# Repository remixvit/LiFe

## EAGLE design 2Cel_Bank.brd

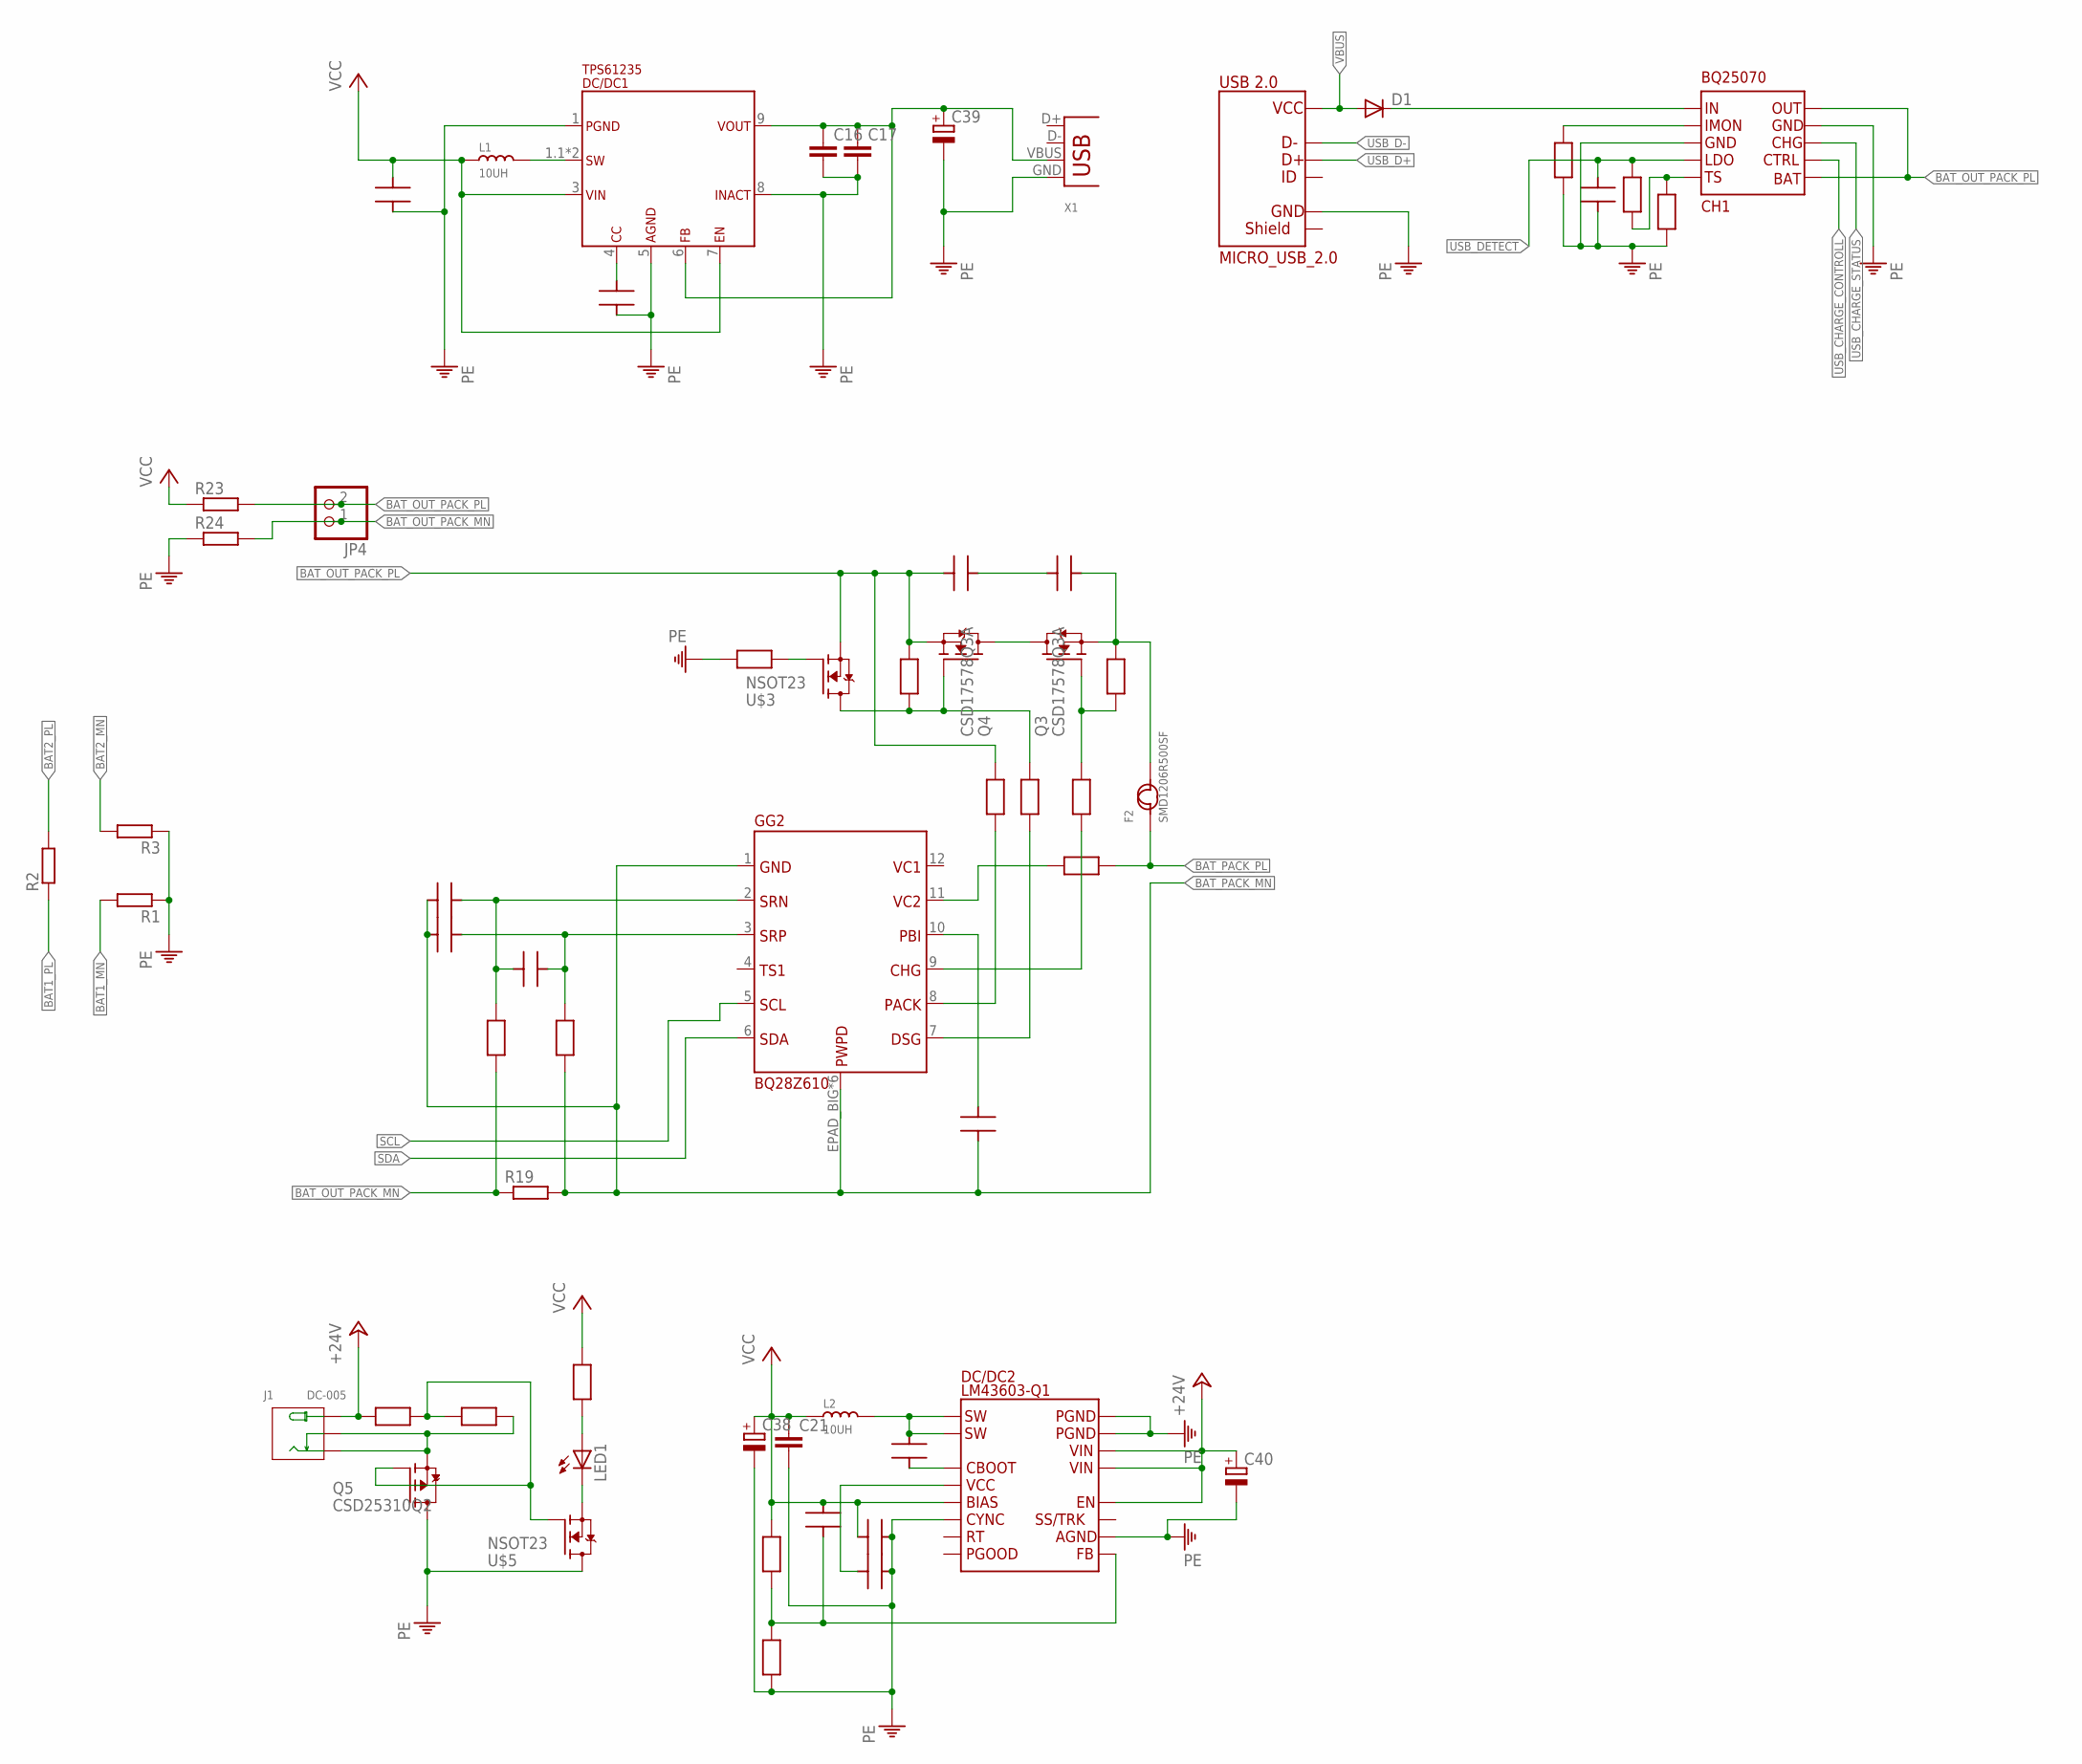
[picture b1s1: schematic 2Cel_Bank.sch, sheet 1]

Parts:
C7, C8, C9, C10, C11, C12, C13, C14, C18, C19, C20, C22, C33: CAP0603; C0603
C16, C17, C21: C-EUC0805; C0805
C38, C39: CPOL-EUSMCA; SMC_A
C40: CPOL-EUSMCD; SMC_D
CH1: BQ25070; DFN10_2X3
D1: DIODE-DO-214AC; DO-214AC
DC/DC1: TPS61235; VQFN9
DC/DC2: LM43603-Q1; HTSSOP16PWP
F2: SMD1206R500SF; F1812
GG2: BQ28Z610; VSON12
J1: DC-005; DCJ3P-14.2X11.0X9.0MM
JP4: PINHD-1X2; 1X02
L1, L2: 10UH; SMD-2P-L6.0XW6.0XH3.0MM
LED1: LEDCHIP-LED0603; CHIP-LED0603
Q3, Q4: CSD17578Q3A; VSONP8
Q5: CSD25310Q2; SON_Q2
R1, R2, R3, R19, R23, R24: R-EU_R1206; R1206
R11, R12, R13, R14, R15, R16, R17, R18, R20, R22, R25, R26, R27, R28, R29, R30, R31: RES0603; R0603
U$3, U$5: NSOT23; SOT23W
USB_CON1: MICRO_USB_2.0; MICRO-USB5+4P-SMD-0.65
X1: USB-A-S

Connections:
+24V: C40.+, DC/DC2.12, DC/DC2.13, DC/DC2.14, J1.+, R25.2
BAT1_MN: R1.2
BAT1_PL: R2.1; also elsewhere on the board
BAT2_MN: R3.2
BAT2_PL: R2.2
BAT_OUT_PACK_MN: JP4.1, R17.1, R19.1, R24.2
BAT_OUT_PACK_PL: C7.1, CH1.P$6, CH1.P$10, JP4.2, Q4.S1 (S), Q4.S2 (S), Q4.S3 (S), R12.2, R15.2, R23.2, U$3.S; also elsewhere on the board
BAT_PACK_MN: C9.1, C10.2, C11.2, GG2.1, GG2.EPAD_BIG, GG2.EPAD_M1, GG2.EPAD_M2, GG2.EPAD_M3, GG2.EPAD_M4, GG2.EPAD_VIA, R18.1, R19.2
BAT_PACK_PL: F2.1, R20.1
unnamed: C8.2, F2.2, Q3.S1 (S), Q3.S2 (S), Q3.S3 (S), R11.2
unnamed: Q3.D1 (D), Q3.D2 (D), Q3.D3 (D), Q3.D4 (D), Q3.D5 (D), Q4.D1 (D), Q4.D2 (D), Q4.D3 (D), Q4.D4 (D), Q4.D5 (D)
unnamed: Q4.G, R12.1, R13.2, U$3.D
unnamed: Q3.G, R11.1, R14.2
unnamed: C7.2, C8.1
unnamed: GG2.9, R14.1
unnamed: GG2.7, R13.1
unnamed: GG2.8, R15.1
unnamed: R16.1, U$3.G
unnamed: C9.2, GG2.10
unnamed: C10.1, C12.2, GG2.2, R17.2
unnamed: C11.1, C12.1, GG2.3, R18.2
unnamed: GG2.11, R20.2
unnamed: J1.-1 (-), J1.-2 (CDN), Q5.4 (D), Q5.D, R26.1
unnamed: DC/DC1.1.1, DC/DC1.1.2, L1.2
unnamed: Q5.3 (G), R25.1, R26.2, U$5.G
unnamed: C13.2, DC/DC1.4
unnamed: C18.2, DC/DC2.1, DC/DC2.2, L2.2
unnamed: C16.1, C17.1, C39.+, DC/DC1.6, DC/DC1.9, X1.VBUS
unnamed: C18.1, DC/DC2.3
unnamed: C19.2, DC/DC2.4
unnamed: C22.2, DC/DC2.9, R27.2, R28.2
unnamed: CH1.P$1, D1.C
unnamed: CH1.P$2, R22.2
unnamed: LED1.C, U$5.S
unnamed: CH1.P$5, R29.2, R30.1
unnamed: LED1.A, R31.2
PE: C13.1, C14.1, C16.2, C17.2, C19.1, C20.1, C21.2, C33.1, C38.-, C39.-, C40.-, CH1.EPAD, CH1.P$3, CH1.P$9, DC/DC1.1, DC/DC1.5, DC/DC1.8, DC/DC2.6, DC/DC2.10, DC/DC2.15, DC/DC2.16, DC/DC2.EXP, Q5.1 (S), Q5.2 (S), Q5.5 (S), Q5.6 (S), Q5.S, R1.1, R3.1, R16.2, R22.1, R24.1, R28.1, R29.1, U$5.D, USB_CON1.5, X1.GND; also elsewhere on the board
SCL: GG2.5; also elsewhere on the board
SDA: GG2.6; also elsewhere on the board
USB_CHARGE_CONTROLL: CH1.P$7; also elsewhere on the board
USB_CHARGE_STATUS: CH1.P$8; also elsewhere on the board
USB_D+: USB_CON1.3; also elsewhere on the board
USB_D-: USB_CON1.2; also elsewhere on the board
USB_DETECT: C33.2, CH1.P$4, R30.2
VBUS: D1.A, USB_CON1.1; also elsewhere on the board
VCC: C14.2, C20.2, C21.1, C22.1, C38.+, DC/DC1.3, DC/DC1.7, DC/DC2.5, L1.1, L2.1, R23.1, R27.1, R31.1

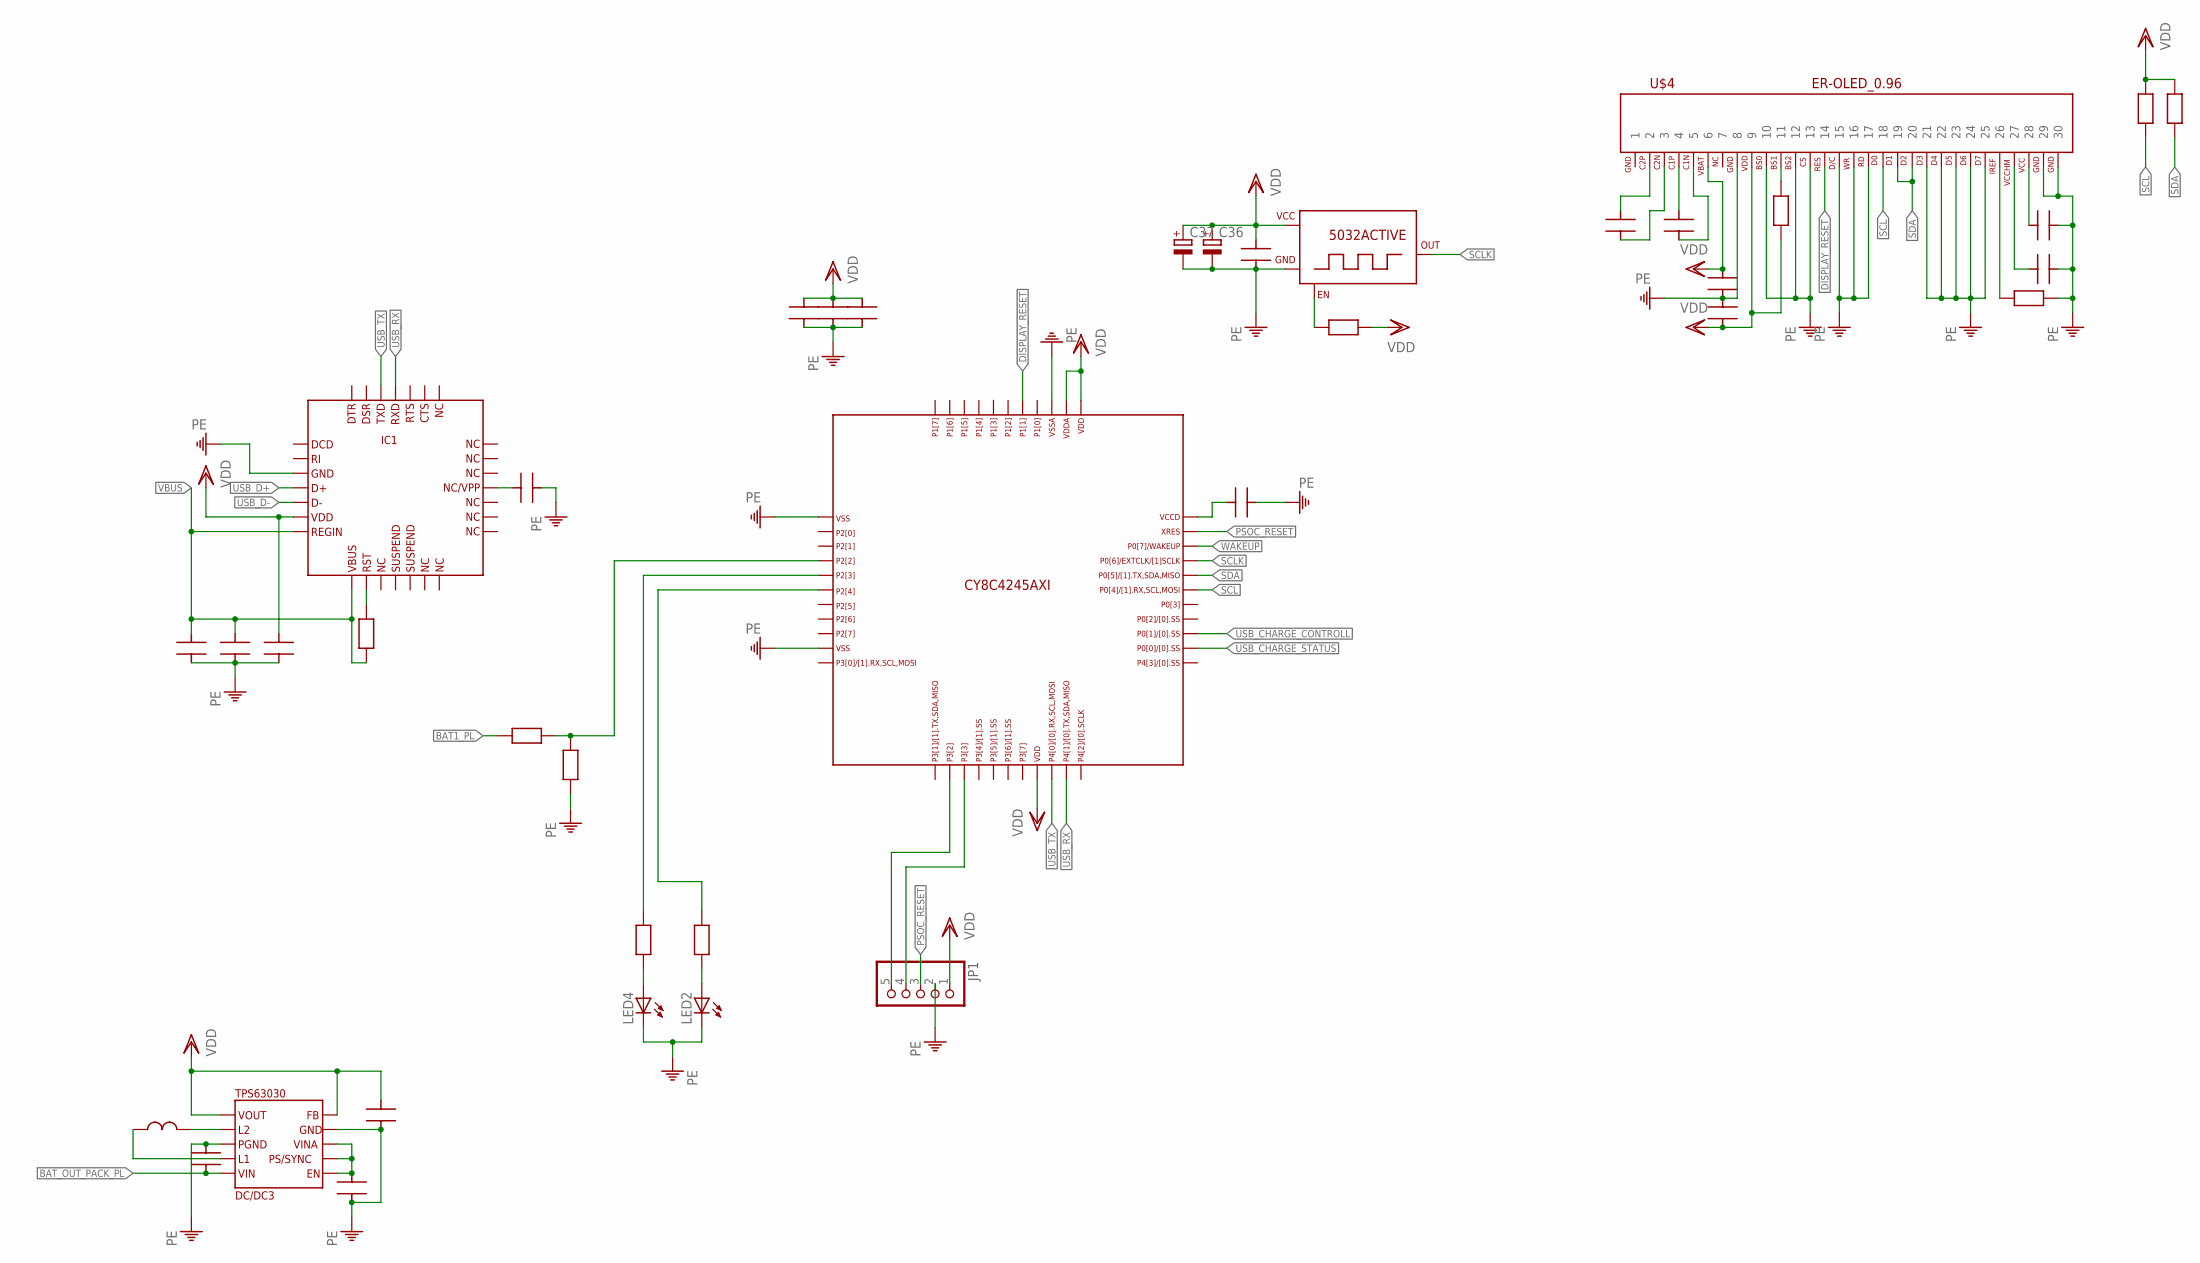
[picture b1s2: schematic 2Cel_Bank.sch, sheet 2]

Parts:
C1, C2, C3, C4, C5, C6, C23, C24, C25, C26, C27, C28, C29, C30, C31, C32, C34, C35: CAP0603; C0603
C36, C37: CPOL-EUSMCA; SMC_A
DC/DC3: TPS63030; WSON10
IC1: CP2102/9; QFN-28
JP1: PINHD-1X5; 1X05
L3: L0603
LED2, LED4: LEDCHIP-LED0603; CHIP-LED0603
R4, R5, R6, R7, R8, R9, R10, R21, R32, R33: RES0603; R0603
U$1: CY8C4245; TQFP44_CY_LOGO
U$2: 5032ACTIVE; 5030A
U$4: ER-OLED_0.96; 30PIN

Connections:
BAT1_PL: R10.2; also elsewhere on the board
BAT_OUT_PACK_PL: C30.2, DC/DC3.P$5; also elsewhere on the board
DISPLAY_RESET: U$1.38, U$4.14
unnamed: C1.2, IC1.18
unnamed: IC1.9, R4.2
unnamed: JP1.5, U$1.13
unnamed: JP1.4, U$1.14
unnamed: C5.2, U$1.33
unnamed: R5.2, U$2.1 (EN)
unnamed: C23.1, U$4.2
unnamed: C24.1, U$4.4
unnamed: C23.2, U$4.3
unnamed: C24.2, U$4.5
unnamed: C28.1, U$4.27
unnamed: R6.2, U$4.26
unnamed: R10.1, R21.1, U$1.4
unnamed: C27.1, U$4.28
unnamed: R7.1, U$4.11
unnamed: DC/DC3.P$2, L3.2
unnamed: DC/DC3.P$4, L3.1
unnamed: C29.1, DC/DC3.P$6, DC/DC3.P$7, DC/DC3.P$8
unnamed: R33.1, U$1.5
unnamed: LED2.A, R32.2
unnamed: LED4.A, R33.2
unnamed: R32.1, U$1.6
PE: C1.1, C2.2, C3.2, C4.2, C5.1, C6.2, C25.1, C26.2, C27.2, C28.2, C29.2, C30.1, C31.2, C32.2, C34.2, C35.2, C36.-, C37.-, DC/DC3.EPAD_B, DC/DC3.EPAD_T, DC/DC3.EPAD_VIA, DC/DC3.P$3, DC/DC3.P$9, IC1.3, IC1.EPAD_B, IC1.EPAD_T, IC1.EPAD_VIA1, IC1.EPAD_VIA2, IC1.EPAD_VIA3, IC1.EPAD_VIA4, IC1.EPAD_VIA5, IC1.EPAD_VIA6, IC1.EPAD_VIA7, IC1.EPAD_VIA8, IC1.EPAD_VIA9, JP1.2, LED2.C, LED4.C, R6.1, R21.2, U$1.1, U$1.10, U$1.36, U$2.2 (GND), U$4.8, U$4.10, U$4.12, U$4.13, U$4.15, U$4.16, U$4.17, U$4.21, U$4.22, U$4.23, U$4.24, U$4.25, U$4.29, U$4.30; also elsewhere on the board
PSOC_RESET: JP1.3, U$1.32
SCL: R8.2, U$1.28, U$4.18; also elsewhere on the board
SCLK: U$1.30, U$2.3 (OUT)
SDA: R9.2, U$1.29, U$4.19, U$4.20; also elsewhere on the board
USB_CHARGE_CONTROLL: U$1.25; also elsewhere on the board
USB_CHARGE_STATUS: U$1.24; also elsewhere on the board
USB_D+: IC1.4; also elsewhere on the board
USB_D-: IC1.5; also elsewhere on the board
USB_RX: IC1.25, U$1.21
USB_TX: IC1.26, U$1.20
VBUS: C2.1, C3.1, IC1.7, IC1.8, R4.1; also elsewhere on the board
VDD: C4.1, C6.1, C25.2, C26.1, C31.1, C32.1, C34.1, C35.1, C36.+, C37.+, DC/DC3.P$1, DC/DC3.P$10, IC1.6, JP1.1, R5.1, R7.2, R8.1, R9.1, U$1.19, U$1.34, U$1.35, U$2.4 (+5V), U$4.6, U$4.9
WAKEUP: U$1.31

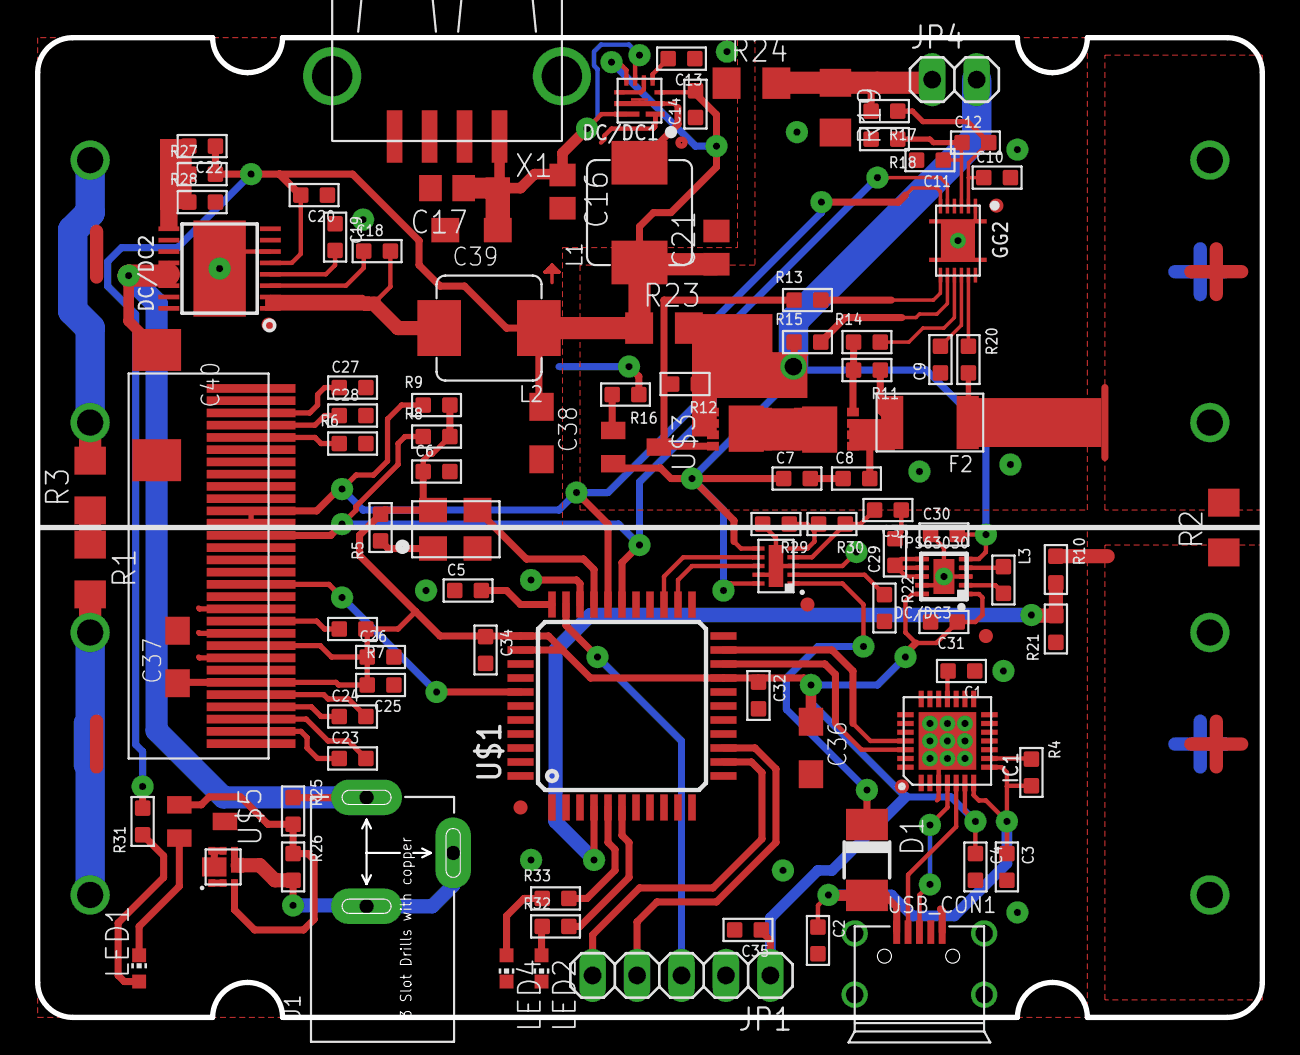
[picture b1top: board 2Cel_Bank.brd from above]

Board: 2 copper layers, 70.0 x 56.0 mm, 99 parts (0 on the bottom side), 71 nets.

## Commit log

2016-02-15 Create PCB
2016-02-16 Route PCB
2016-03-02 Complite Route
